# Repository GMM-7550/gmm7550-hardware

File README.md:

# CologneChip GateMate FPGA Module: GMM-7550

**January 2026 Update**

USB 3 adapter board is out of production, RP2040 firmware
is running, and basic functionality is tested -- no hardware
issues discovered.

**October 2025 Update**

USB 3 adapter board is ready for production after the
[schematic](./doc/USB3-GMM-7550_1.0_2025-10-10.pdf)
changes and layout. KiCad 3D render of the board:

**July 2025 Update**

An experimental USB 3 Adapter board schematic is ready for
layout:

[USB 3 Adapter revision 0.9](./doc/USB3-GMM-7550_0.9_2025-07-24.pdf)

**January 2024 Update**

The project repositories are moved to a dedicated account.
Please, update your references to <https://github.com/gmm-7550/>
to follow further development.

**June 2022 Update**
After more than two years of development and delays
the module and adapter boards are out of production.

Tests are underway, no problems discovered so far, updates
are expected in a few weeks.

This project is licensed under [CERN-OHL-P v2](./cern_ohl_p_v2.txt)

Current module revision is 2.1 -- it is updated to the latest
(flip-chip) GateMate FPGA pin out. The other changes are complete
redesigns of the power and clock subsystems due to component
availability.

[Schematic (pdf) version 2.1](./doc/GMM-7550_2.1_2022-04-24.pdf)

## 40-pin GPIO (R-Pi HAT) Adapter for GMM-7550 Module

The adapter board provides power to the GMM-7550 module (5V from
40-pin GPIO or from an external connector), I2C and SPI interfaces,
control over the module power enable and reset signals and module
power consumption monitoring.

Two 12-pin Pmod extension connectors are routed to the GateMate
FPGA South GPIO pins through 2.5/3.3 bi-directional level converter.

[Schematic (pdf) version 1.1](./doc/HAT-GMM-7550_1.1_2022-04-24.pdf)

## Memory Extension Module

The module provides 512Kx8 static RAM (CY7C1049GN30-10ZSXI) with 10 ns
access time and 16 MiB QSPI NOR FLASH (S25LP128-JBLE). The module may
be connected to P1, P2 or P3 connector of the GMM-7550, up to three
modules may be connected simultaneously. An SPI Bridge example design
for FPGA routes SPI from a host (R-Pi or VisionFive board) to the
module connector and allows to access the SPI NOR chip on the module
from the host. The module control software provides commands to
automate the FPGA configuration and access to the SPI on the extension
module.

[Schematic (pdf) version 1.0](./doc/MEM-GMM-7550_1.0_2023-04-24.pdf)

## Test and Demo System based on VisionFive RISC-V SBC

The SBC runs [`buildroot`](https://buildroot.org/) embedded Linux,
experimental
[configuration for the VisionFive board](https://github.com/ak-fau/buildroot-visionfive/)
is available as a `buildroot`-external tree.

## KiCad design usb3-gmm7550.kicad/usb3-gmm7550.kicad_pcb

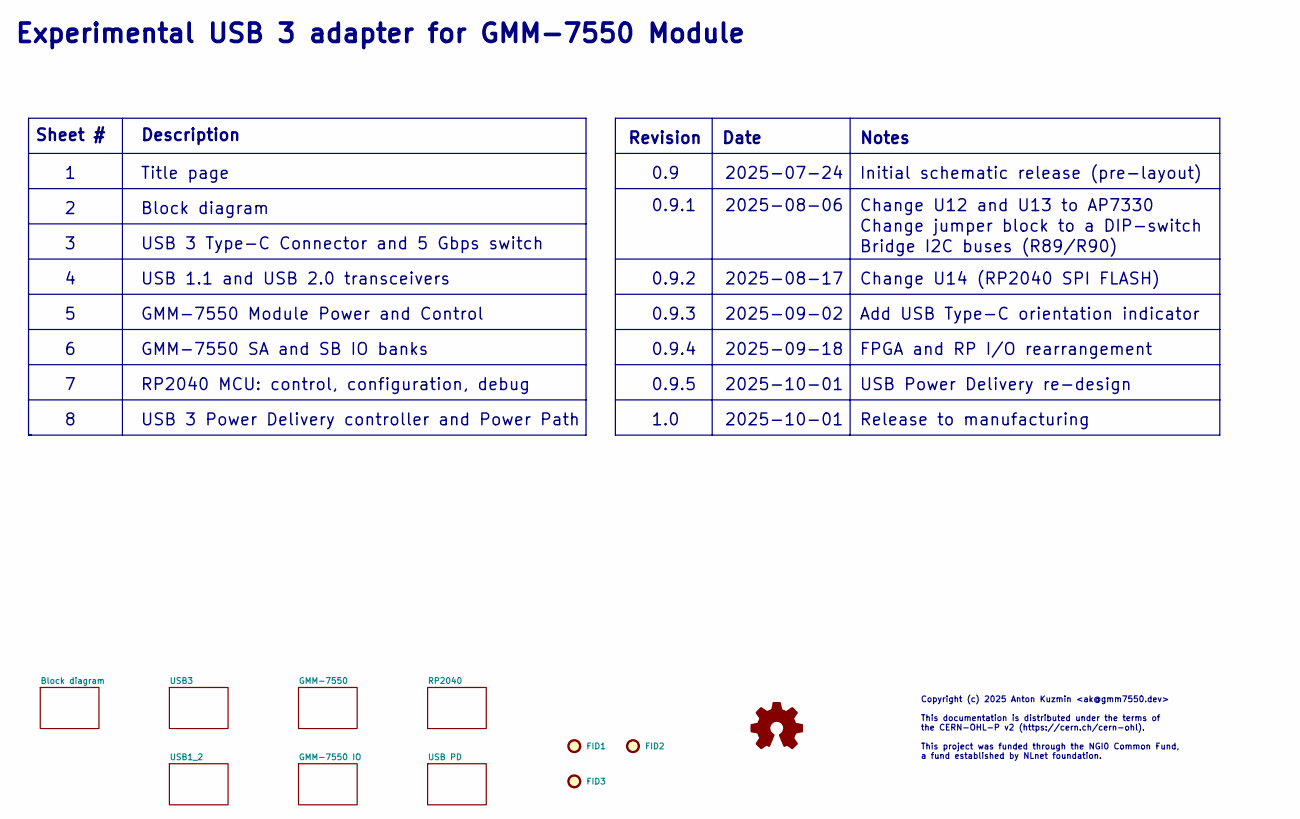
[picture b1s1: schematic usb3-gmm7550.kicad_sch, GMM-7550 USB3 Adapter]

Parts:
FID1, FID2, FID3: Fiducial; Fiducial_1mm_Mask2mm

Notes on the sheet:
Sheet #
Bridge I2C buses (R89/R90)
0.9
2025-09-02
Change U12 and U13 to AP7330
USB Power Delivery re-design
Revision
Title page
Release to manufacturing
2025-08-17
USB 1.1 and USB 2.0 transceivers
FPGA and RP I/O rearrangement
2025-09-18
Notes
Change U14 (RP2040 SPI FLASH)
GMM-7550 SA and SB IO banks
Date
USB 3 Type-C Connector and 5 Gbps switch
0.9.5
0.9.1
Block diagram
RP2040 MCU: control, configuration, debug
1.0
Experimental USB 3 adapter for GMM-7550 Module
USB 3 Power Delivery controller and Power Path
Initial schematic release (pre-layout)
0.9.2
0.9.3
2025-07-24
Change jumper block to a DIP-switch
2025-10-01
2025-08-06
Copyright (c) 2025 Anton Kuzmin <ak@gmm7550.dev> This documentation is distributed under the terms of the CERN-OHL-P v2 (https://cern.ch/cern-ohl). This project was funded through the NGI0 Common Fund, a fund established by NLnet foundation.
Add USB Type-C orientation indicator
Description
0.9.4
GMM-7550 Module Power and Control

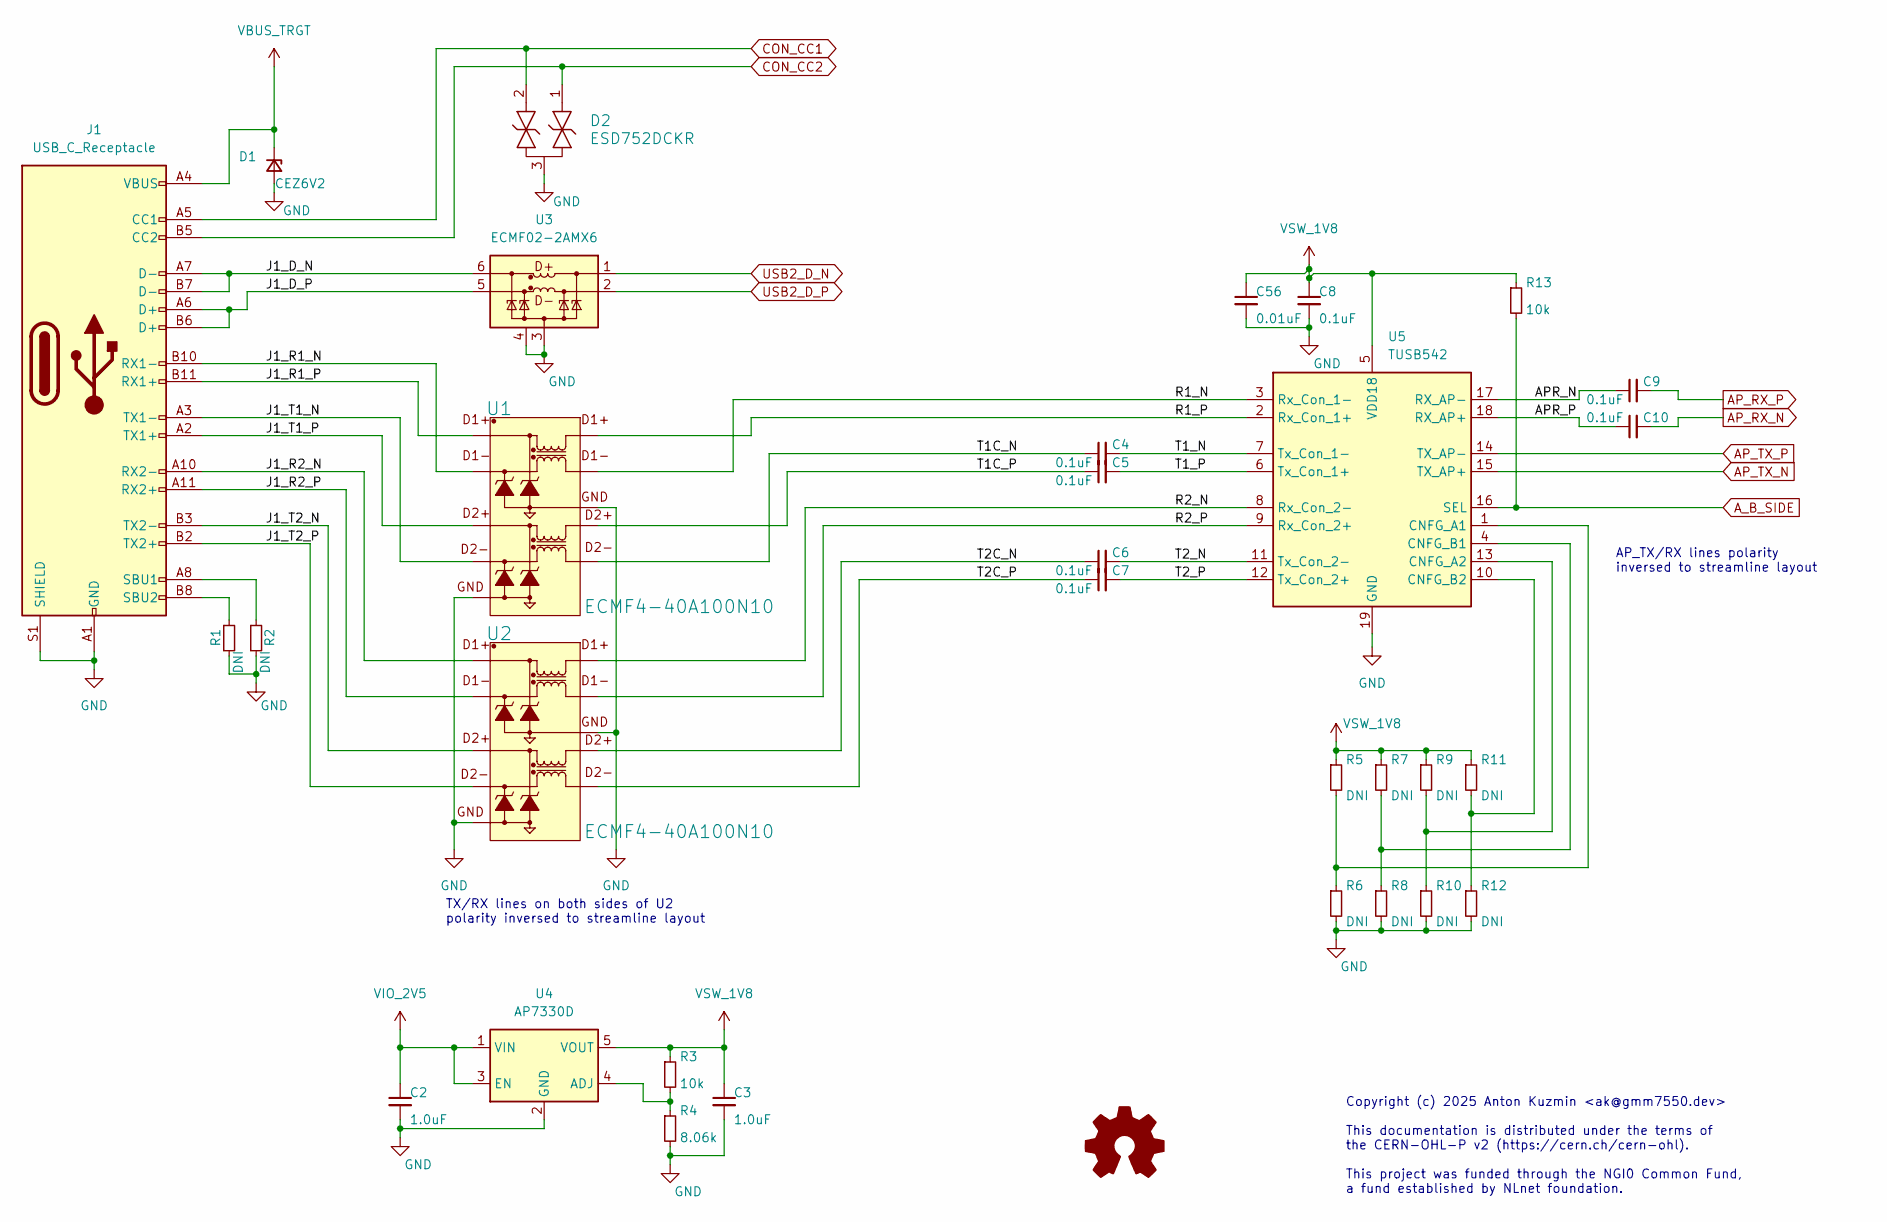
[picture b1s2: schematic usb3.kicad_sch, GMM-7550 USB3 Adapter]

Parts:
C2, C3: 1.0uF; C_0402_1005Metric
C4, C5, C6, C7, C8, C9, C10: 0.1uF; C_0402_1005Metric
C56: 0.01uF; C_0402_1005Metric
D1: CEZ6V2; D_SOD-523
D2: ESD752DCKR; SOT-SC70_DCK_TEX
J1: USB_C_Receptacle; USB_C_Receptacle_Molex_105450-0101
R1, R2, R5, R6, R7, R8, R9, R10, R11, R12: DNI; R_0402_1005Metric
R3, R13: 10k; R_0402_1005Metric
R4: 8.06k; R_0402_1005Metric
U1, U2: ECMF4-40A100N10; UQFN10L_1P4X2P25X0P4_STM
U3: ECMF02-2AMX6; ST_UQFN-6L_1.5x1.7mm_P0.5mm
U4: AP7330D; SOT-23-5
U5: TUSB542; Texas_X2QFN-18-1EP_2x2.4mm_P0.4mm_EP1x1.4mm_ThermalVias

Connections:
/USB3/APR_N: C9.1, U5.17 (RX_AP-)
/USB3/APR_P: C10.1, U5.18 (RX_AP+)
/USB3/J1_D_N: J1.A7 (D-), J1.B7 (D-), U3.6 (D+_out)
/USB3/J1_D_P: J1.A6 (D+), J1.B6 (D+), U3.5 (D-_out)
/USB3/J1_R1_N: J1.B10 (RX1-), U1.2 (D1-)
/USB3/J1_R1_P: J1.B11 (RX1+), U1.1 (D1+)
/USB3/J1_R2_N: J1.A10 (RX2-), U2.1 (D1+)
/USB3/J1_R2_P: J1.A11 (RX2+), U2.2 (D1-)
/USB3/J1_T1_N: J1.A3 (TX1-), U1.5 (D2-)
/USB3/J1_T1_P: J1.A2 (TX1+), U1.4 (D2+)
/USB3/J1_T2_N: J1.B3 (TX2-), U2.4 (D2+)
/USB3/J1_T2_P: J1.B2 (TX2+), U2.5 (D2-)
/USB3/R1_N: U1.9 (D1-1), U5.3 (Rx_Con_1-)
/USB3/R1_P: U1.10 (D1+1), U5.2 (Rx_Con_1+)
/USB3/R2_N: U2.10 (D1+1), U5.8 (Rx_Con_2-)
/USB3/R2_P: U2.9 (D1-1), U5.9 (Rx_Con_2+)
/USB3/T1C_N: C4.1, U1.6 (D2-1)
/USB3/T1C_P: C5.1, U1.7 (D2+1)
/USB3/T1_N: C4.2, U5.7 (Tx_Con_1-)
/USB3/T1_P: C5.2, U5.6 (Tx_Con_1+)
/USB3/T2C_N: C6.1, U2.7 (D2+1)
/USB3/T2C_P: C7.1, U2.6 (D2-1)
/USB3/T2_N: C6.2, U5.11 (Tx_Con_2-)
/USB3/T2_P: C7.2, U5.12 (Tx_Con_2+)
AP_RX_N: C10.2; also elsewhere on the board
AP_RX_P: C9.2; also elsewhere on the board
AP_TX_N: U5.15 (TX_AP+); also elsewhere on the board
AP_TX_P: U5.14 (TX_AP-); also elsewhere on the board
A_B_SIDE: R13.2, U5.16 (SEL); also elsewhere on the board
CON_CC1: D2.2, J1.A5 (CC1); also elsewhere on the board
CON_CC2: D2.1, J1.B5 (CC2); also elsewhere on the board
GND: C2.2, C3.2, C8.2, C56.2, D1.2 (A), D2.3, J1.A1 (GND), J1.A12 (GND), J1.B1 (GND), J1.B12 (GND), J1.S1 (SHIELD), R1.2, R2.2, R4.2, R6.2, R8.2, R10.2, R12.2, U1.3 (GND), U1.8 (GND1), U2.3 (GND), U2.8 (GND1), U3.3 (GND), U3.4 (NC), U4.2 (GND), U5.19 (GND); also elsewhere on the board
unnamed: J1.A8 (SBU1), R2.1
unnamed: J1.B8 (SBU2), R1.1
unnamed: R3.2, R4.1, U4.4 (ADJ)
unnamed: R5.2, R6.1, U5.1 (CNFG_A1)
unnamed: R9.2, R10.1, U5.13 (CNFG_A2)
unnamed: R7.2, R8.1, U5.4 (CNFG_B1)
unnamed: R11.2, R12.1, U5.10 (CNFG_B2)
USB2_D_N: U3.1 (D+_in); also elsewhere on the board
USB2_D_P: U3.2 (D-_in); also elsewhere on the board
VBUS_TRGT: D1.1 (K), J1.A4 (VBUS), J1.A9 (VBUS), J1.B4 (VBUS), J1.B9 (VBUS); also elsewhere on the board
VIO_2V5: C2.1, U4.1 (VIN), U4.3 (EN); also elsewhere on the board
VSW_1V8: C3.1, C8.1, C56.1, R3.1, R5.1, R7.1, R9.1, R11.1, R13.1, U4.5 (VOUT), U5.5 (VDD18)

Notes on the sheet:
Copyright (c) 2025 Anton Kuzmin <ak@gmm7550.dev> This documentation is distributed under the terms of the CERN-OHL-P v2 (https://cern.ch/cern-ohl). This project was funded through the NGI0 Common Fund, a fund established by NLnet foundation.
TX/RX lines on both sides of U2 polarity inversed to streamline layout
AP_TX/RX lines polarity inversed to streamline layout

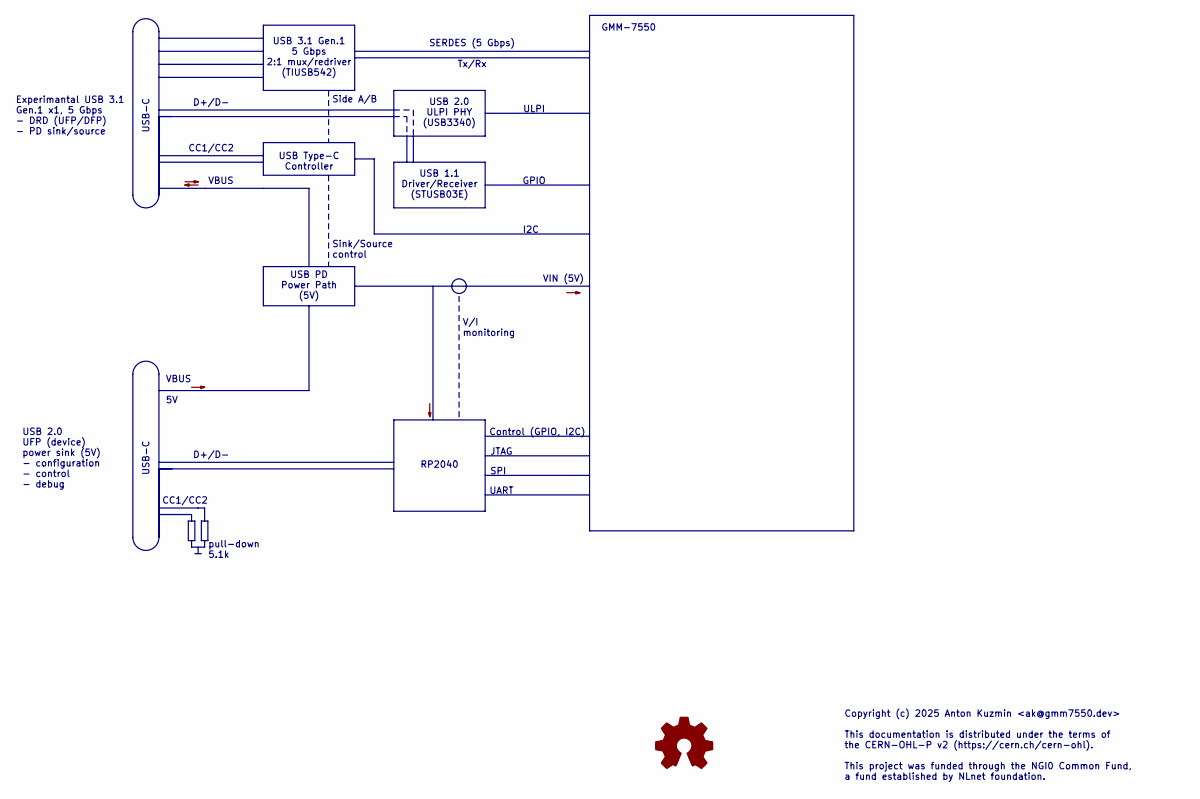
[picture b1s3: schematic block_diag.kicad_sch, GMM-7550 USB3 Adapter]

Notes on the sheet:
USB PD Power Path (5V)
Sink/Source control
USB Type-C Controller
Side A/B
CC1/CC2
ULPI
D+/D-
GMM-7550
USB 2.0 ULPI PHY (USB3340)
Copyright (c) 2025 Anton Kuzmin <ak@gmm7550.dev> This documentation is distributed under the terms of the CERN-OHL-P v2 (https://cern.ch/cern-ohl). This project was funded through the NGI0 Common Fund, a fund established by NLnet foundation.
SPI
VBUS 5V
pull-down 5.1k
UART
USB-C
Experimantal USB 3.1 Gen.1 x1, 5 Gbps - DRD (UFP/DFP) - PD sink/source
Control (GPIO, I2C)
USB 2.0 UFP (device) power sink (5V) - configuration - control - debug
USB 1.1 Driver/Receiver (STUSB03E)
VBUS
SERDES (5 Gbps) Tx/Rx
JTAG
I2C
V/I monitoring
GPIO
RP2040
USB 3.1 Gen.1 5 Gbps 2:1 mux/redriver (TIUSB542)
VIN (5V)

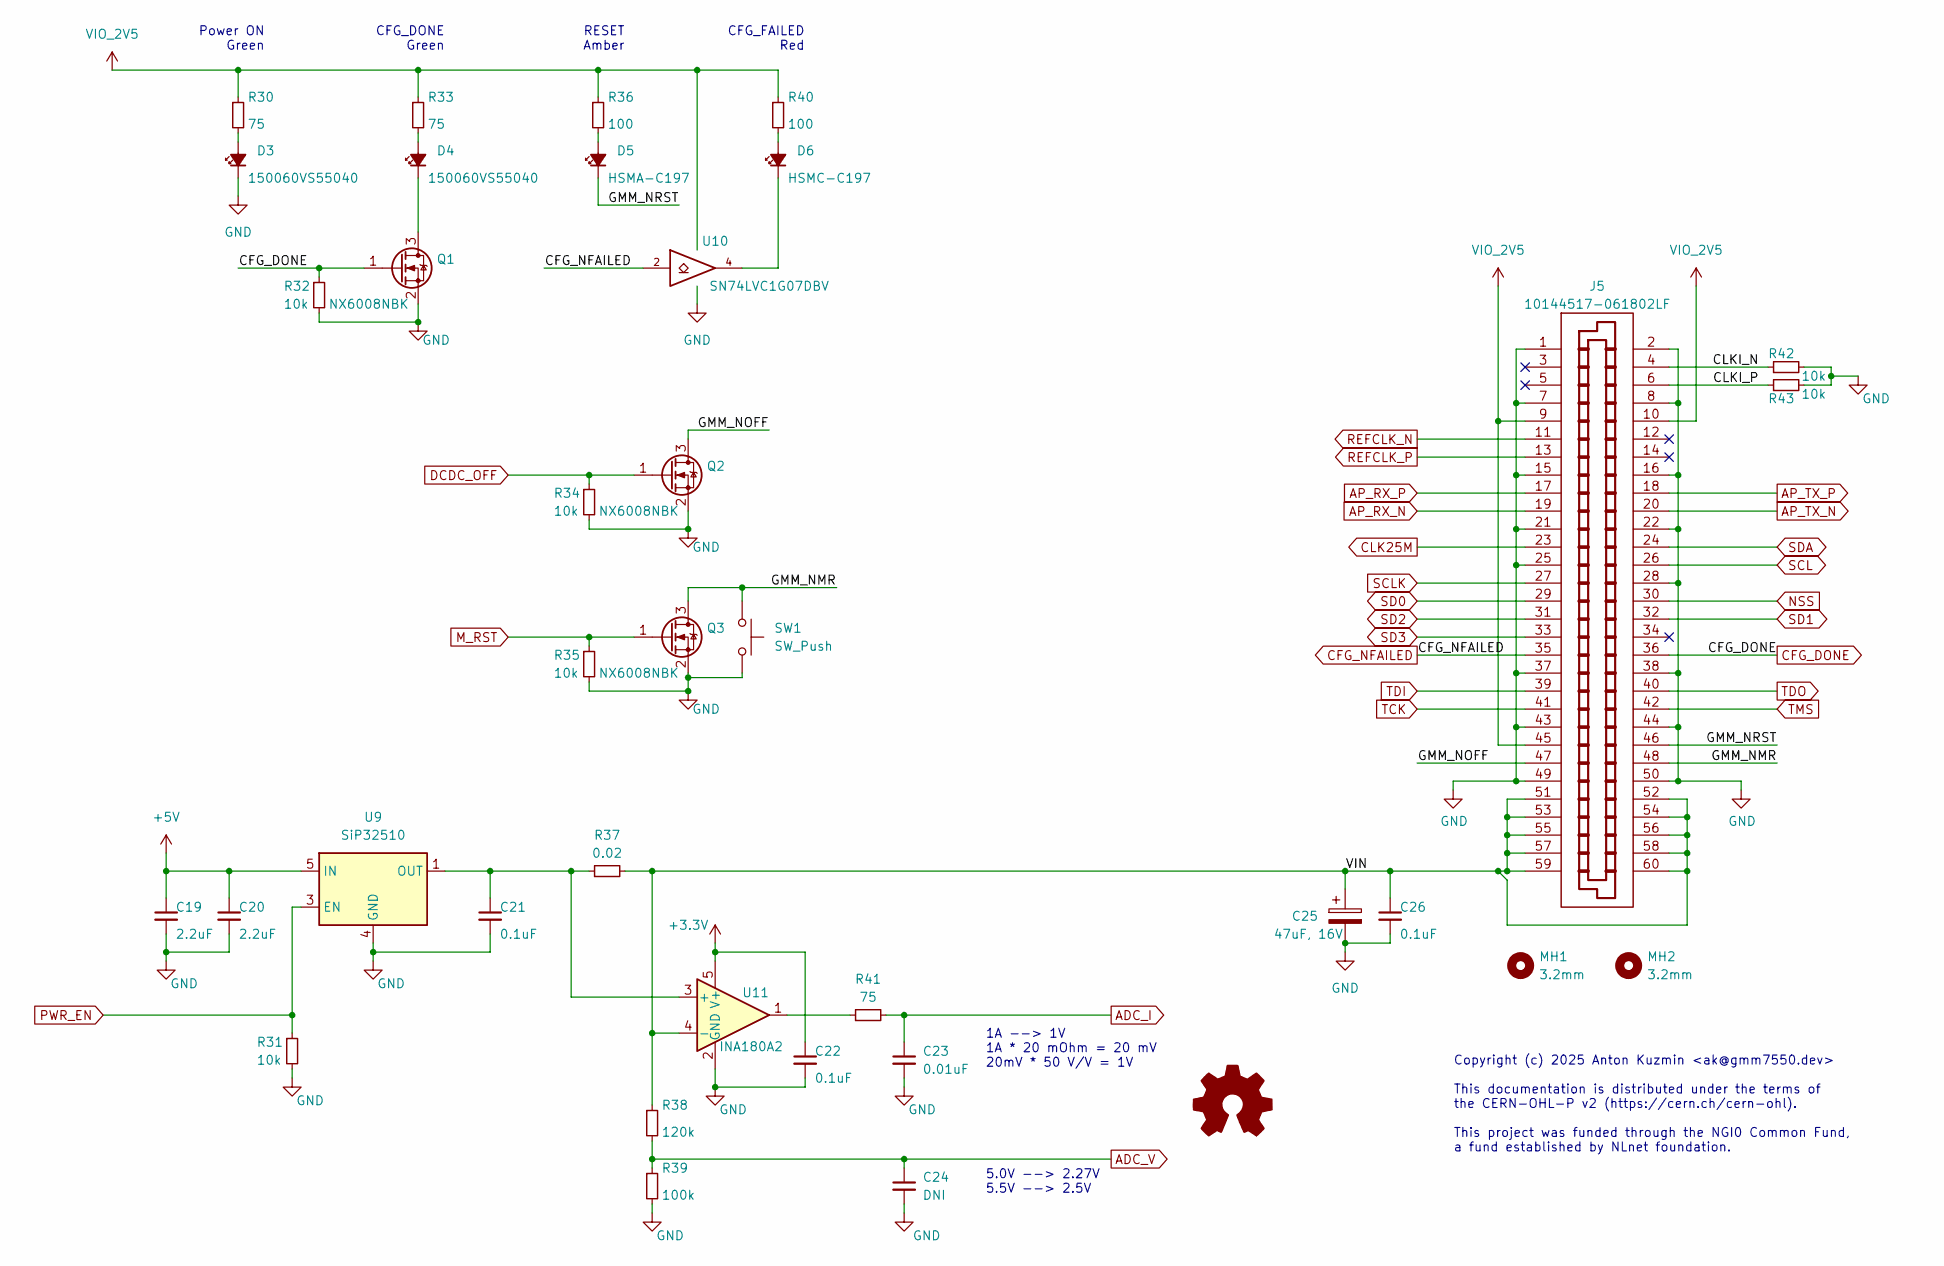
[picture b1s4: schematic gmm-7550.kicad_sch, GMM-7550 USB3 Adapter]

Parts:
C19, C20: 2.2uF; C_0603_1608Metric
C21, C22, C26: 0.1uF; C_0402_1005Metric
C23: 0.01uF; C_0402_1005Metric
C24: DNI; C_0402_1005Metric
C25: 47uF, 16V; CP_EIA-6032-28_Kemet-C
D3, D4: 150060VS55040; LED_0603_1608Metric
D5: HSMA-C197; LED_0603_1608Metric
D6: HSMC-C197; LED_0603_1608Metric
J5: 10144517-061802LF
MH1, MH2: 3.2mm; MountingHole_3.2mm_M3_ISO7380
Q1, Q2, Q3: NX6008NBK; SOT-23
R30, R33, R41: 75; R_0402_1005Metric
R31, R32, R34, R35, R42, R43: 10k; R_0402_1005Metric
R36, R40: 100; R_0402_1005Metric
R37: 0.02; R_0805_2012Metric; MPN PE0805FRE470R02Z
R38: 120k; R_0402_1005Metric
R39: 100k; R_0402_1005Metric
SW1: SW_Push; SW_SPST_PTS810
U9: SiP32510; SOT-23-6
U10: SN74LVC1G07DBV; SOT-23-5
U11: INA180A2; SOT-23-5

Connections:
+3.3V: C22.1, U11.5 (V+); also elsewhere on the board
+5V: C19.1, C20.1, U9.5 (IN), U9.6 (IN); also elsewhere on the board
/GMM-7550/CLKI_N: J5.4, R42.1
/GMM-7550/CLKI_P: J5.6, R43.1
/GMM-7550/GMM_NMR: J5.48, Q3.3 (D), SW1.1
/GMM-7550/GMM_NOFF: J5.47, Q2.3 (D)
/GMM-7550/GMM_NRST: D5.1 (K), J5.46
/GMM-7550/VIN: C25.1, C26.1, J5.51, J5.52, J5.53, J5.54, J5.55, J5.56, J5.57, J5.58, J5.59, J5.60, R37.2, R38.1, U11.4 (-)
ADC_I: C23.1, R41.2; also elsewhere on the board
ADC_V: C24.1, R38.2, R39.1; also elsewhere on the board
AP_RX_N: J5.19; also elsewhere on the board
AP_RX_P: J5.17; also elsewhere on the board
AP_TX_N: J5.20; also elsewhere on the board
AP_TX_P: J5.18; also elsewhere on the board
CFG_DONE: J5.36, Q1.1 (G), R32.1; also elsewhere on the board
CFG_NFAILED: J5.35, U10.2; also elsewhere on the board
CLK25M: J5.23; also elsewhere on the board
DCDC_OFF: Q2.1 (G), R34.1; also elsewhere on the board
GND: C19.2, C20.2, C21.2, C22.2, C23.2, C24.2, C25.2, C26.2, D3.1 (K), J5.1, J5.2, J5.7, J5.8, J5.15, J5.16, J5.21, J5.22, J5.25, J5.28, J5.37, J5.38, J5.43, J5.44, J5.49, J5.50, Q1.2 (S), Q2.2 (S), Q3.2 (S), R31.2, R32.2, R34.2, R35.2, R39.2, R42.2, R43.2, SW1.2, U9.4 (GND), U10.3 (GND), U11.2 (GND); also elsewhere on the board
M_RST: Q3.1 (G), R35.1; also elsewhere on the board
NSS: J5.30; also elsewhere on the board
unnamed: D3.2 (A), R30.2
unnamed: D4.2 (A), R33.2
unnamed: D4.1 (K), Q1.3 (D)
unnamed: D5.2 (A), R36.2
unnamed: D6.2 (A), R40.2
unnamed: D6.1 (K), U10.4
unnamed: R41.1, U11.1
unnamed: C21.1, R37.1, U9.1 (OUT), U9.2 (OUT), U11.3 (+)
PWR_EN: R31.1, U9.3 (EN); also elsewhere on the board
REFCLK_N: J5.11; also elsewhere on the board
REFCLK_P: J5.13; also elsewhere on the board
SCL: J5.26; also elsewhere on the board
SCLK: J5.27; also elsewhere on the board
SD0: J5.29; also elsewhere on the board
SD1: J5.32; also elsewhere on the board
SD2: J5.31; also elsewhere on the board
SD3: J5.33; also elsewhere on the board
SDA: J5.24; also elsewhere on the board
TCK: J5.41; also elsewhere on the board
TDI: J5.39; also elsewhere on the board
TDO: J5.40; also elsewhere on the board
TMS: J5.42; also elsewhere on the board
VIO_2V5: J5.9, J5.10, J5.45, R30.1, R33.1, R36.1, R40.1, U10.5 (VCC); also elsewhere on the board

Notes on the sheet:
5.0V --> 2.27V 5.5V --> 2.5V
RESET Amber
CFG_FAILED Red
CFG_DONE Green
Copyright (c) 2025 Anton Kuzmin <ak@gmm7550.dev> This documentation is distributed under the terms of the CERN-OHL-P v2 (https://cern.ch/cern-ohl). This project was funded through the NGI0 Common Fund, a fund established by NLnet foundation.
1A --> 1V 1A * 20 mOhm = 20 mV 20mV * 50 V/V = 1V
Power ON Green

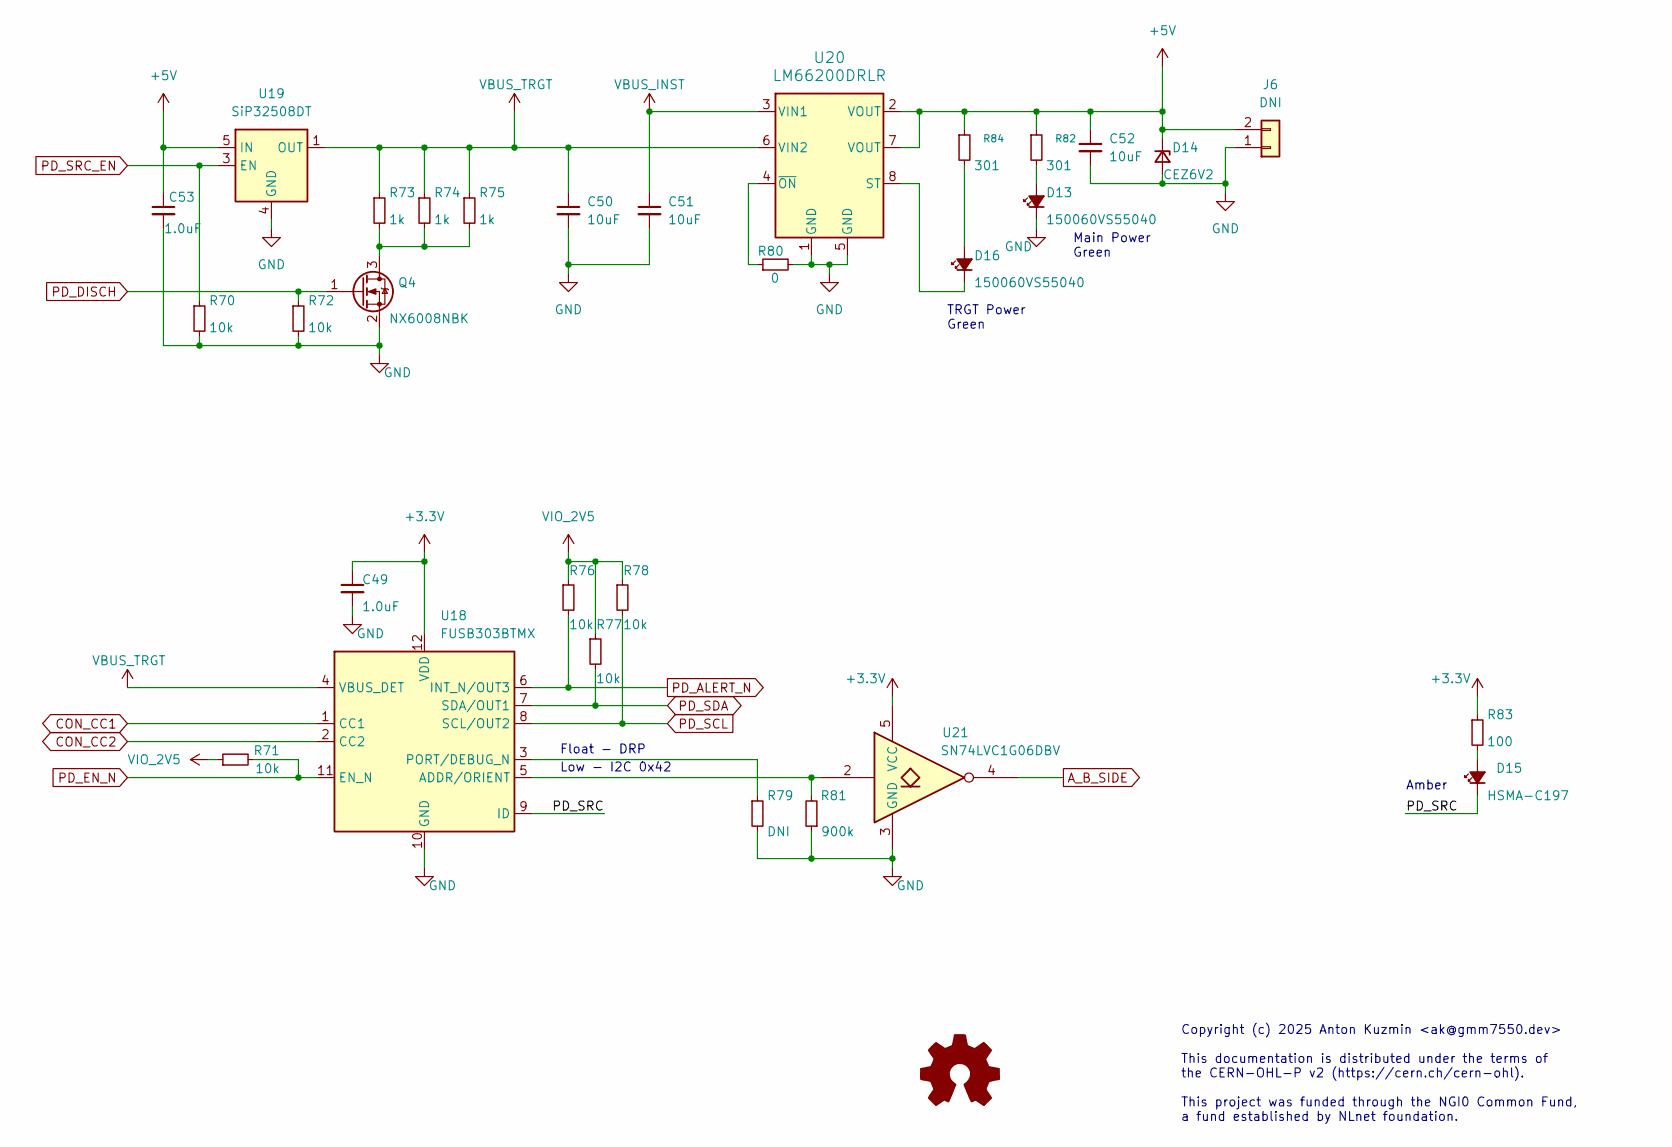
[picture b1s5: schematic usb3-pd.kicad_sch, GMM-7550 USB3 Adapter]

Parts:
C49, C53: 1.0uF; C_0402_1005Metric
C50, C51, C52: 10uF; C_0805_2012Metric
D13, D16: 150060VS55040; LED_0603_1608Metric
D14: CEZ6V2; D_SOD-523
D15: HSMA-C197; LED_0603_1608Metric
J6: DNI; Molex_Micro-Fit_3.0_43045-0200_2x01_P3.00mm_Horizontal
Q4: NX6008NBK; SOT-23
R70, R71, R72, R76, R77, R78: 10k; R_0402_1005Metric
R73, R74, R75: 1k; R_0402_1005Metric
R79: DNI; R_0402_1005Metric
R80: 0; R_0402_1005Metric
R81: 900k; R_0402_1005Metric
R82, R84: 301; R_0402_1005Metric
R83: 100; R_0402_1005Metric
U18: FUSB303BTMX; OnSemi_X2QFN-12_1.6x1.6mm; Manufacturer_Part_Number FUSB303BTMX; Mouser Part Number 863-FUSB303BTMX
U19: SiP32508DT; TSOT-23-6
U20: LM66200DRLR; SOT-5X3_DRL_TEX
U21: SN74LVC1G06DBV; SOT-23-5

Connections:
+3.3V: C49.1, R83.1, U18.12 (VDD), U21.5 (VCC); also elsewhere on the board
+5V: C52.1, C53.1, D14.1 (K), J6.2, R82.1, R84.1, U19.5 (IN), U19.6 (IN), U20.2 (VOUT), U20.7 (VOUT); also elsewhere on the board
/USB PD/PD_SRC: D15.1 (K), U18.9 (ID)
A_B_SIDE: U21.4; also elsewhere on the board
CON_CC1: U18.1 (CC1); also elsewhere on the board
CON_CC2: U18.2 (CC2); also elsewhere on the board
GND: C49.2, C50.2, C51.2, C52.2, C53.2, D13.1 (K), D14.2 (A), J6.1, Q4.2 (S), R70.2, R72.2, R79.2, R80.2, R81.1, U18.10 (GND), U19.4 (GND), U20.1 (GND), U20.5 (GND), U21.3 (GND); also elsewhere on the board
unnamed: D13.2 (A), R82.2
unnamed: D15.2 (A), R83.2
unnamed: D16.2 (A), R84.2
unnamed: D16.1 (K), U20.8 (ST)
unnamed: Q4.3 (D), R73.2, R74.2, R75.2
unnamed: R81.2, U18.5 (ADDR/ORIENT), U21.2
unnamed: R79.1, U18.3 (PORT/DEBUG_N)
unnamed: R80.1, U20.4 (~ON)
PD_ALERT_N: R76.2, U18.6 (INT_N/OUT3); also elsewhere on the board
PD_DISCH: Q4.1 (G), R72.1; also elsewhere on the board
PD_EN_N: R71.2, U18.11 (EN_N); also elsewhere on the board
PD_SCL: R78.2, U18.8 (SCL/OUT2); also elsewhere on the board
PD_SDA: R77.2, U18.7 (SDA/OUT1); also elsewhere on the board
PD_SRC_EN: R70.1, U19.3 (EN); also elsewhere on the board
VBUS_INST: C51.1, U20.3 (VIN1); also elsewhere on the board
VBUS_TRGT: C50.1, R73.1, R74.1, R75.1, U18.4 (VBUS_DET), U19.1 (OUT), U19.2 (OUT), U20.6 (VIN2); also elsewhere on the board
VIO_2V5: R71.1, R76.1, R77.1, R78.1; also elsewhere on the board

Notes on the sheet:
Amber
Copyright (c) 2025 Anton Kuzmin <ak@gmm7550.dev> This documentation is distributed under the terms of the CERN-OHL-P v2 (https://cern.ch/cern-ohl). This project was funded through the NGI0 Common Fund, a fund established by NLnet foundation.
Float - DRP
Low - I2C 0x42
Main Power Green
TRGT Power Green

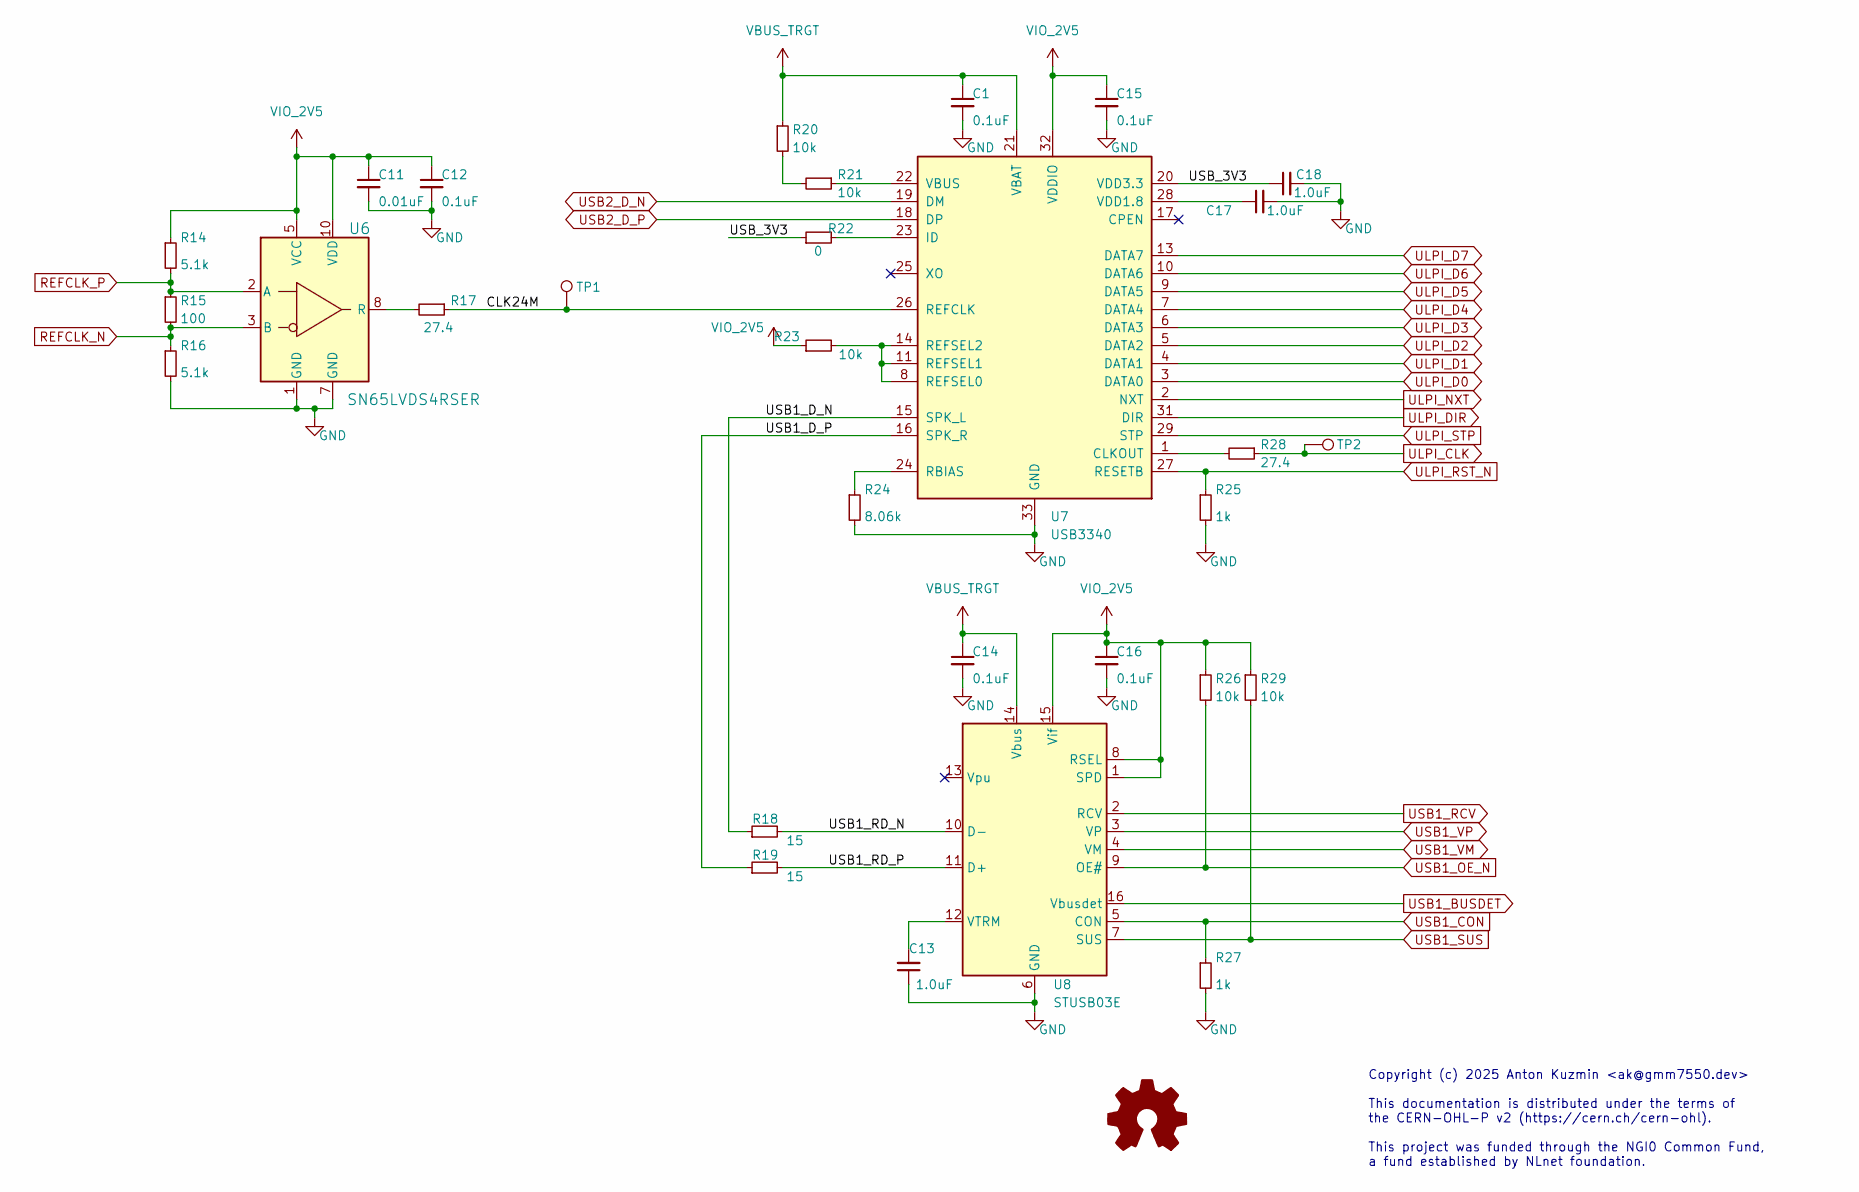
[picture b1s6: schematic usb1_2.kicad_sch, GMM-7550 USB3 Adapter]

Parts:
C1, C12, C14, C15, C16: 0.1uF; C_0402_1005Metric
C11: 0.01uF; C_0402_1005Metric
C13, C17, C18: 1.0uF; C_0402_1005Metric
R14, R16: 5.1k; R_0402_1005Metric
R15: 100; R_0402_1005Metric
R17, R28: 27.4; R_0402_1005Metric
R18, R19: 15; R_0402_1005Metric
R20, R21, R23, R26, R29: 10k; R_0402_1005Metric
R22: 0; R_0402_1005Metric
R24: 8.06k; R_0402_1005Metric
R25, R27: 1k; R_0402_1005Metric
TP1, TP2: TestPoint; TestPoint_Pad_D1.0mm
U6: SN65LVDS4RSER; RSE10
U7: USB3340; QFN-32-1EP_5x5mm_P0.5mm_EP3.3x3.3mm_ThermalVias
U8: STUSB03E; QFN-16-1EP_3x3mm_P0.5mm_EP1.7x1.7mm

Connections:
/USB1_2/CLK24M: R17.1, TP1.1, U7.26 (REFCLK)
/USB1_2/USB1_D_N: R18.1, U7.15 (SPK_L)
/USB1_2/USB1_D_P: R19.1, U7.16 (SPK_R)
/USB1_2/USB1_RD_N: R18.2, U8.10 (D-)
/USB1_2/USB1_RD_P: R19.2, U8.11 (D+)
/USB1_2/USB_3V3: C18.1, R22.1, U7.20 (VDD3.3)
GND: C1.2, C11.2, C12.2, C13.1, C14.2, C15.2, C16.2, C17.2, C18.2, R16.2, R24.2, R25.2, R27.2, U6.1 (GND), U6.7 (GND), U7.33 (GND), U8.6 (GND); also elsewhere on the board
unnamed: R20.2, R21.2
unnamed: R17.2, U6.8 (R)
unnamed: R28.2, U7.1 (CLKOUT)
unnamed: R22.2, U7.23 (ID)
unnamed: R24.1, U7.24 (RBIAS)
unnamed: R23.2, U7.8 (REFSEL0), U7.11 (REFSEL1), U7.14 (REFSEL2)
unnamed: R21.1, U7.22 (VBUS)
unnamed: C17.1, U7.28 (VDD1.8)
unnamed: C13.2, U8.12 (VTRM)
REFCLK_N: R15.2, R16.1, U6.3 (B); also elsewhere on the board
REFCLK_P: R14.2, R15.1, U6.2 (A); also elsewhere on the board
ULPI_CLK: R28.1, TP2.1; also elsewhere on the board
ULPI_D0: U7.3 (DATA0); also elsewhere on the board
ULPI_D1: U7.4 (DATA1); also elsewhere on the board
ULPI_D2: U7.5 (DATA2); also elsewhere on the board
ULPI_D3: U7.6 (DATA3); also elsewhere on the board
ULPI_D4: U7.7 (DATA4); also elsewhere on the board
ULPI_D5: U7.9 (DATA5); also elsewhere on the board
ULPI_D6: U7.10 (DATA6); also elsewhere on the board
ULPI_D7: U7.13 (DATA7); also elsewhere on the board
ULPI_DIR: U7.31 (DIR); also elsewhere on the board
ULPI_NXT: U7.2 (NXT); also elsewhere on the board
ULPI_RST_N: R25.1, U7.27 (RESETB); also elsewhere on the board
ULPI_STP: U7.29 (STP); also elsewhere on the board
USB1_BUSDET: U8.16 (Vbusdet); also elsewhere on the board
USB1_CON: R27.1, U8.5 (CON); also elsewhere on the board
USB1_OE_N: R26.2, U8.9 (OE#); also elsewhere on the board
USB1_RCV: U8.2 (RCV); also elsewhere on the board
USB1_SUS: R29.2, U8.7 (SUS); also elsewhere on the board
USB1_VM: U8.4 (VM); also elsewhere on the board
USB1_VP: U8.3 (VP); also elsewhere on the board
USB2_D_N: U7.19 (DM); also elsewhere on the board
USB2_D_P: U7.18 (DP); also elsewhere on the board
VBUS_TRGT: C1.1, C14.1, R20.1, U7.21 (VBAT), U8.14 (Vbus); also elsewhere on the board
VIO_2V5: C11.1, C12.1, C15.1, C16.1, R14.1, R23.1, R26.1, R29.1, U6.5 (VCC), U6.10 (VDD), U7.32 (VDDIO), U8.1 (SPD), U8.8 (RSEL), U8.15 (Vif); also elsewhere on the board

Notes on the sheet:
Copyright (c) 2025 Anton Kuzmin <ak@gmm7550.dev> This documentation is distributed under the terms of the CERN-OHL-P v2 (https://cern.ch/cern-ohl). This project was funded through the NGI0 Common Fund, a fund established by NLnet foundation.
